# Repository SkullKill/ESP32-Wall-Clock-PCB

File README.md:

# ESP32-Wall-Clock-PCB
ESP32 based 30cm Wall Mounted Clock. WiFi, NTP, SNMP, web interface, MicroUsb, Type-C, HG3613 Retrofit

Can be retrofitted into a HG3613 Case, or use standalone with the wall mounting on the pcb, or in a 3D Printed Case.

3D Printable Case not done yet...

this is still a work in progress.

PCB itself should be final, but the software is still being worked on. 

e.g Code for the light sensitivity sensor to automaticly adjust the display intensity

RTC PCF8563T code. 

OLED coding, etc....

ESP32-Wall-Clock-01.jpg

ESP32-Wall-Clock-Front-RT-V1.0a-WithOLEDboard.jpg

## V 1.0 26/08/2020 - Initial Release

  ------------------------------------------------------------
## PCB Board Used

Ready to use PCB Board (no up yet)

https://www.skstore.com.au/electronics/pcb/ESP32-Wall-Clock

PCB Design Files / gerber files

[ESP32-Wall-Clock-PCB](https://github.com/SkullKill/ESP32-Wall-Clock-PCB)

3D Printed Case design files / STL (no up yet)

[ESP32-Wall-Clock-PCB](https://github.com/SkullKill/ESP32-Wall-Clock-PCB)

FYI Gerber files are in the release section

https://github.com/SkullKill/ESP32-Wall-Clock-PCB/releases

more pictures in the wiki

https://github.com/SkullKill/ESP32-Wall-Clock-PCB/wiki

ESP32-Wall-Clock-HG3613-Retrofit-04.jpg

  ------------------------------------------------------------
## Schematics

ESP32-Wall-Clock-schematics-01-V1.0a.jpg

ESP32-Wall-Clock-schematics-02-V1.0.jpg

ESP32-Wall-Clock-schematics-03-V1.0.jpg

  ------------------------------------------------------------
## MecanicalDrawing

(Not Done Yet)

  ------------------------------------------------------------
## Code Used
(Not Done Yet)
[ESP32-Wall-Clock](https://github.com/SkullKill/ESP32-Wall-Clock)

  ------------------------------------------------------------

PCB features

* ESP32 Microprocessor
* onboard, IO0 / Reset switches
* breakout for UART (Programming/Serial monitor), i2c, SPI, 1-wire
* 5V input via MicroUSB, USB Type-C, 2.1mm barrel, Screw Type Terminal
* OR 5.6V to 26V if using Switchmode Reg, OR 6.4V-30V if using AMS1117-5.0 (input via 2.1mm barrel or Screw Type Terminal)
* PCF8563T RTC Clock with CR2032 Coin Cell Battery
* CP2102 USB to Serial, with Auto Reset (optional)
* RTC clock
* ALS-PT19 Light Intensity Sensor, to adjust Screen Brightness
* AHT20 Temperature / Humidity Sensor
* 1-Wire provision (possibility to add a number of DS18B20 temperature sensors)
* Built in buzzer
* 1-wire rail (possibility to add a number of DS18B20 temperature sensors)
* 2 physical button, + 8 physical button via TM1638, using diode, so that multiple button can be pressed at the same time.
* Ability to add external buttons.
* 1 configurable status light. (IO 13)
* 2 X TM1638 LED Segment Display Driver (in Common Anode Mode) [ one driving 6 digit, one driving 10 digit ]
* 6 X 1.8" / 45mm Segment display for Time Display (Common Anode Mode)
* 0.56" / 14.22mm Segment display for Date/Month / Temperature/Humidity (Common Anode Mode)
* Micro SD Card Slot
* Reverse polarity protection on 12V input
* PTC Fuse
* Level Shifter for ESP32 - TM1638 Comms

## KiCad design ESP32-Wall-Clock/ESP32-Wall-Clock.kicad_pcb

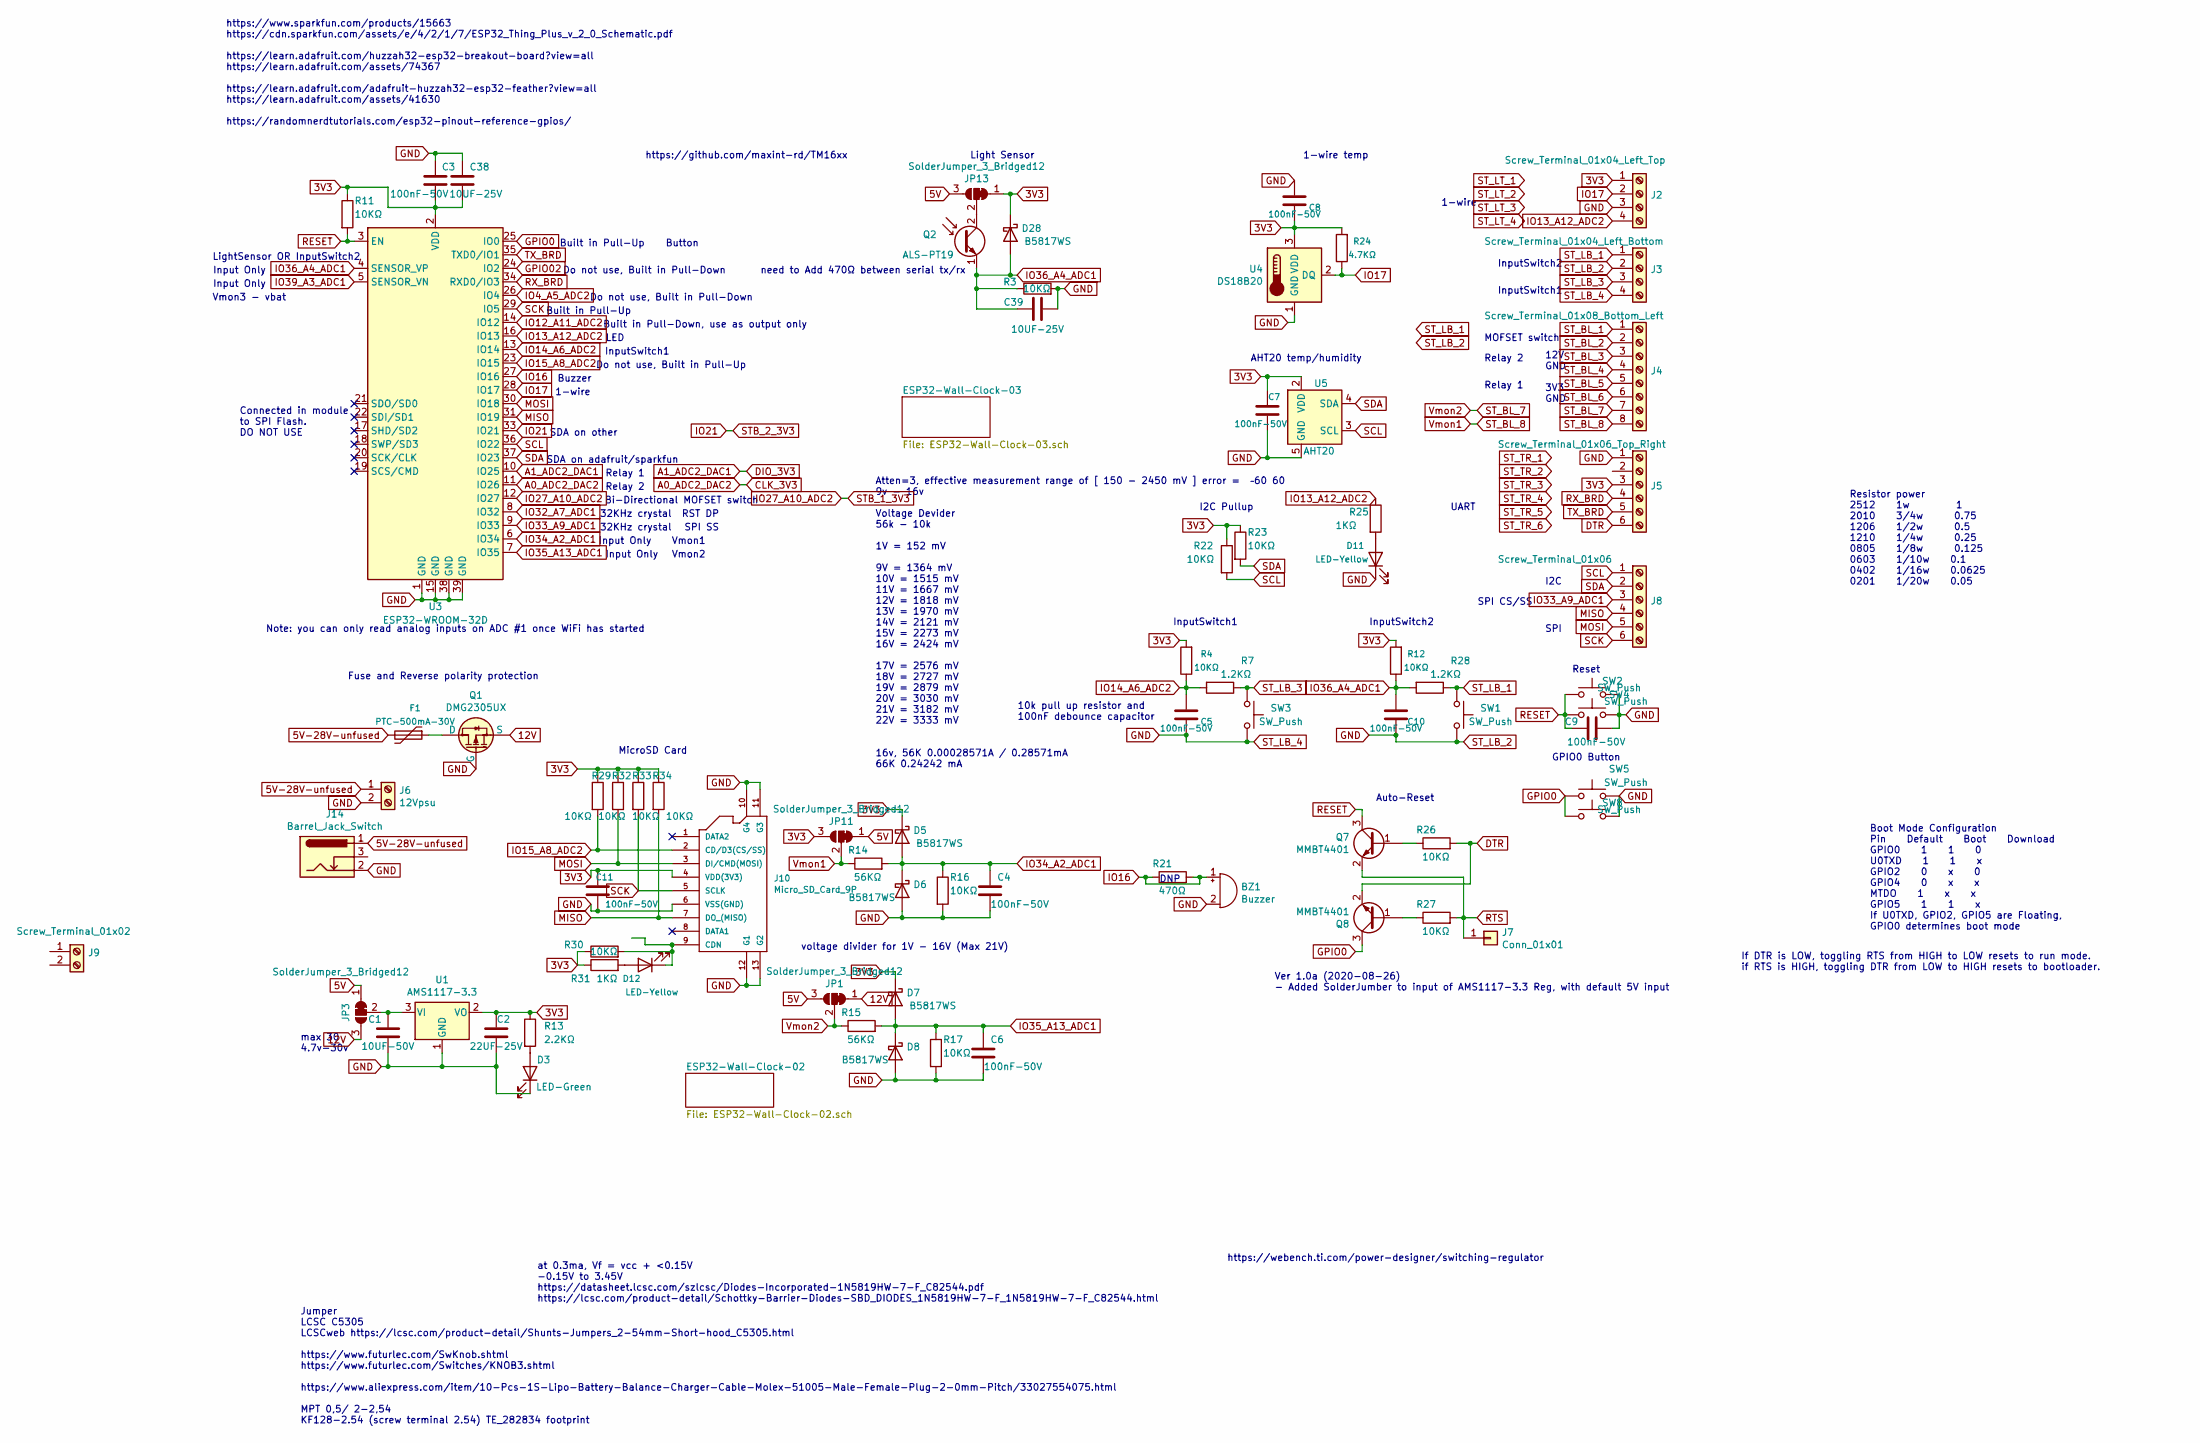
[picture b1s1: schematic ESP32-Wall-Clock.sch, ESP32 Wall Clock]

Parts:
BZ1: Buzzer; Buzzer_12x9.5RM5.0; MPN ZL-YDW1207-4005PA-5.0; LCSC C219727
C1: 10UF-50V; C_1206_3216Metric; MPN CL31A106KBHNNNE; LCSC C13585
C2: 22UF-25V; C_0805_2012Metric; MPN CL21A226MAQNNNE; LCSC C45783
C3, C4, C5, C6, C7, C8, C9, C10, C11: 100nF-50V; C_0603_1608Metric; MPN AC0603KRX7R9BB104; LCSC C149620
C38, C39: 10UF-25V; C_0603_1608Metric; MPN CL10A106MA8NRNC; LCSC C96446
D3: LED-Green; LED_0603_1608Metric; MPN ORH-G36G; LCSC C205443
D5, D6, D7, D8, D28: B5817WS; D_SOD-323; MPN B5817WS-SJ; LCSC C114023
D11, D12: LED-Yellow; LED_0603_1608Metric; MPN FC-DA1608HYK-588J; LCSC C84268
F1: PTC-500mA-30V; Fuse_1812_4532Metric; MPN JK-MSMD050-30; LCSC C369168
J2: Screw_Terminal_01x04_Left_Top; TerminalBlock_TE_282834-4_1x04_P2.54mm_Horizontal; MPN KF128-2.54-4P
J3: Screw_Terminal_01x04_Left_Bottom; TerminalBlock_TE_282834-4_1x04_P2.54mm_Horizontal; MPN KF128-2.54-4P
J4: Screw_Terminal_01x08_Bottom_Left; TerminalBlock_TE_282834-8_1x08_P2.54mm_Horizontal; MPN KF128-2.54-8P
J5: Screw_Terminal_01x06_Top_Right; TerminalBlock_TE_282834-6_1x06_P2.54mm_Horizontal; MPN KF128-2.54-6P
J6: 12Vpsu; TerminalBlock_bornier-2_P5.08mm; MPN WJ126V-5.0-2P; LCSC C8404
J7: Conn_01x01; PinHeader_1x01_P2.54mm_Vertical
J8: Screw_Terminal_01x06; TerminalBlock_TE_282834-6_1x06_P2.54mm_Horizontal; MPN KF128-2.54-6P
J9: Screw_Terminal_01x02; TerminalBlock_TE_282834-2_1x02_P2.54mm_Horizontal; MPN KF128-2.54-2P
J10: Micro_SD_Card_9P; Micro_SD_9+4P-SMD-16.1X14.5X1.85MM; MPN XKTF-015-N; LCSC C381082
J14: Barrel_Jack_Switch; BarrelJack_Wuerth_6941xx301002; MPN DC-005 5.5-2.0MM; LCSC C16214
JP1, JP11, JP13: SolderJumper_3_Bridged12; SolderJumper-3_P1.3mm_Bridged12_RoundedPad1.0x1.5mm
JP3: SolderJumper_3_Bridged12; SolderJumper-3_P1.3mm_Bridged2Bar12_RoundedPad1.0x1.5mm
Q1: DMG2305UX; SOT-23; MPN DMG2305UX-13; LCSC C144153
Q2: ALS-PT19; LED_0603_1608Metric; MPN ALS-PT19-315C/L177/TR8; LCSC C146233
Q7, Q8: MMBT4401; SOT-23; MPN MMBT4401LT1G; LCSC C31776
R3, R4, R11, R12, R16, R17, R22, R23, R26, R27, R29, R30, R32, R33, R34: 10KΩ; R_0603_1608Metric; MPN RC0603FR-0710KL; LCSC C98220
R7, R28: 1.2KΩ; R_0603_1608Metric; MPN RC0603FR-071K2L; LCSC C114605
R13: 2.2KΩ; R_0603_1608Metric; MPN RC0603FR-072K2L; LCSC C114662
R14, R15: 56KΩ; R_0603_1608Metric; MPN RC0603FR-0756KL; LCSC C114630
R21: 470Ω; R_0603_1608Metric; MPN RC0603FR-07470RL; LCSC C114669
R24: 4.7KΩ; R_0603_1608Metric; MPN RC0603FR-074K7L; LCSC C99782
R25, R31: 1KΩ; R_0603_1608Metric; MPN RC0603FR-071KL; LCSC C22548
SW1, SW2, SW3, SW8: SW_Push; SW_Push_1P1T-MP_NO_Horizontal_Alps_SKRTLAE010; MPN SKRTLAE010; LCSC C110293
SW4, SW5: SW_Push; SW_SPST_TL3305A; LCSC C174049
U1: AMS1117-3.3; SOT-223-3_TabPin2; MPN AMS1117-3.3; LCSC C426566
U3: ESP32-WROOM-32D; ESP32-WROOM-32; LCSC C473012
U4: DS18B20; TO-92_Inline; MPN DS18B20+; LCSC C9753
U5: AHT20; MPN AHT20; LCSC C503357

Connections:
3V3: C2.1, C3.1, C7.1, C8.2, C11.1, C38.2, D5.1 (K), D7.1 (K), D28.1 (K), J2.1, J5.3, J10.4 (VDD(3V3)), JP11.3 (B), JP13.1 (A), R4.2, R11.1, R12.2, R13.1, R22.1, R23.1, R24.2, R29.1, R30.1, R31.1, R32.1, R33.1, R34.1, U1.2 (VO), U3.2 (VDD), U4.3 (VDD), U5.2 (VDD); also elsewhere on the board
5V: JP1.3 (B), JP3.1 (A), JP11.1 (A), JP13.3 (B); also elsewhere on the board
5V-28V-unfused: F1.2, J6.1, J14.1
12V: JP1.1 (A), JP3.3 (B), Q1.2 (S); also elsewhere on the board
A0_ADC2_DAC2: U3.11 (IO26); also elsewhere on the board
A1_ADC2_DAC1: U3.10 (IO25); also elsewhere on the board
DTR: J5.6, Q8.2 (E), R26.2; also elsewhere on the board
GND: BZ1.2 (+), C1.2, C2.2, C3.2, C4.2, C5.2, C6.2, C7.2, C8.1, C9.2, C10.2, C11.2, C38.1, C39.2, D3.1 (K), D6.2 (A), D8.2 (A), D11.1 (K), J2.3, J3.2, J3.4, J5.1, J6.2, J10.6 (VSS(GND)), J10.10 (G4), J10.11 (G3), J10.12 (G1), J10.13 (G2), J14.2, Q1.1 (G), R3.2, R16.2, R17.2, SW1.2, SW2.2, SW3.2, SW4.2, SW5.2, SW8.2, U1.1 (GND), U3.1 (GND), U3.15 (GND), U3.38 (GND), U3.39 (GND), U4.1 (GND), U5.5 (GND); also elsewhere on the board
GPIO0: Q8.3 (C), SW5.1, SW8.1, U3.25 (IO0)
GPIO02: U3.24 (IO2)
IO4_A5_ADC2: U3.26 (IO4)
IO12_A11_ADC2: U3.14 (IO12)
IO13_A12_ADC2: J2.4, R25.1, U3.16 (IO13)
IO14_A6_ADC2: C5.1, R4.1, R7.2, U3.13 (IO14)
IO15_A8_ADC2: J10.2 (CD/D3(CS/SS)), R29.2, U3.23 (IO15)
IO16: BZ1.1 (-), R21.1, R21.2, U3.27 (IO16)
IO17: J2.2, R24.1, U3.28 (IO17), U4.2 (DQ)
IO21: U3.33 (IO21); also elsewhere on the board
IO27_A10_ADC2: U3.12 (IO27); also elsewhere on the board
IO32_A7_ADC1: U3.8 (IO32); also elsewhere on the board
IO33_A9_ADC1: J8.3, U3.9 (IO33)
IO34_A2_ADC1: C4.1, D5.2 (A), D6.1 (K), R14.2, R16.1, U3.6 (IO34)
IO35_A13_ADC1: C6.1, D7.2 (A), D8.1 (K), R15.2, R17.1, U3.7 (IO35)
IO36_A4_ADC1: C10.1, C39.1, D28.2 (A), Q2.1 (E), R3.1, R12.1, R28.2, U3.4 (SENSOR_VP)
IO39_A3_ADC1: U3.5 (SENSOR_VN); also elsewhere on the board
MISO: J8.4, J10.7 (DO_(MISO)), R34.2, U3.31 (IO19)
MOSI: J8.5, J10.3 (DI/CMD(MOSI)), R32.2, U3.30 (IO18)
unnamed: C1.1, JP3.2 (C), U1.3 (VI)
unnamed: D3.2 (A), R13.2
unnamed: D11.2 (A), R25.2
unnamed: D12.1 (K), J10.9 (CDN), R30.2
unnamed: D12.2 (A), R31.2
unnamed: F1.1, Q1.3 (D)
unnamed: JP13.2 (C), Q2.2 (C)
unnamed: Q7.1 (B), R26.1
unnamed: Q8.1 (B), R27.1
RESET: C9.1, Q7.3 (C), R11.2, SW2.1, SW4.1, U3.3 (EN); also elsewhere on the board
RTS: J7.1, Q7.2 (E), R27.2; also elsewhere on the board
RX_BRD: J5.4, U3.34 (RXD0/IO3); also elsewhere on the board
SCK: J8.6, J10.5 (SCLK), R33.2, U3.29 (IO5)
SCL: J8.1, R22.2, U3.36 (IO22), U5.3 (SCL); also elsewhere on the board
SDA: J8.2, R23.2, U3.37 (IO23), U5.4 (SDA); also elsewhere on the board
ST_BL_7: J4.7, JP1.2 (C), R15.1
ST_BL_8: J4.8, JP11.2 (C), R14.1
ST_LB_1: J3.1, R28.1, SW1.1
ST_LB_3: J3.3, R7.1, SW3.1
TX_BRD: J5.5, U3.35 (TXD0/IO1); also elsewhere on the board

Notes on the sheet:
https://webench.ti.com/power-designer/switching-regulator
Ver 1.0a (2020-08-26) - Added SolderJumber to input of AMS1117-3.3 Reg, with default 5V input
10k pull up resistor and 100nF debounce capacitor
Jumper LCSC C5305 LCSCweb https://lcsc.com/product-detail/Shunts-Jumpers_2-54mm-Short-hood_C5305.html https://www.futurlec.com/SwKnob.shtml https://www.futurlec.com/Switches/KNOB3.shtml https://www.aliexpress.com/item/10-Pcs-1S-Lipo-Battery-Balance-Charger-Cable-Molex-51005-Male-Female-Plug-2-0mm-P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
Fuse and Reverse polarity protection
Resistor power 2512 1w 1 2010 3/4w 0.75 1206 1/2w 0.5 1210 1/4w 0.25 0805 1/8w 0.125 0603 1/10w 0.1 0402 1/16w 0.0625 0201 1/20w 0.05
12V GND 3V3 GND
MOFSET switch
InputSwitch1
max 30 4.7v-30v
UART
Relay 1
Atten=3, effective measurement range of [ 150 - 2450 mV ] error = –60 60 9v - 16v Voltage Devider 56k - 10k 1V = 152 mV 9V = 1364 mV 10V = 1515 mV 11V = 1667 mV 12V = 1818 mV 13V = 1970 mV 14V = 2121 mV 15V = 2273 mV 16V = 2424 mV 17V = 2576 mV 18V = 2727 mV 19V = 2879 mV 20V = 3030 mV 21V = 3182 m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
at 0.3ma, Vf = vcc + <0.15V -0.15V to 3.45V https://datasheet.lcsc.com/szlcsc/Diodes-Incorporated-1N5819HW-7-F_C82544.pdf https://lcsc.com/product-detail/Schottky-Barrier-Diodes-SBD_DIODES_1N5819HW-7-F_1N5819HW-7-F_C82544.html
https://www.sparkfun.com/products/15663 https://cdn.sparkfun.com/assets/e/4/2/1/7/ESP32_Thing_Plus_v_2_0_Schematic.pdf https://learn.adafruit.com/huzzah32-esp32-breakout-board?view=all https://learn.adafruit.com/assets/74367 https://learn.adafruit.com/adafruit-huzzah32-esp32-feather?view=all https: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
Reset
GPIO0 Button
If DTR is LOW, toggling RTS from HIGH to LOW resets to run mode. if RTS is HIGH, toggling DTR from LOW to HIGH resets to bootloader.
Auto-Reset
Boot Mode Configuration Pin Default Boot Download GPIO0 1 1 0 U0TXD 1 1 x GPIO2 0 x 0 GPIO4 0 x x MTDO 1 x x GPIO5 1 1 x If U0TXD, GPIO2, GPIO5 are Floating, GPIO0 determines boot mode
Vmon1
LED
Button
Note: you can only read analog inputs on ADC #1 once WiFi has started
Input Only
Built in Pull-Down, use as output only
32KHz crystal
1-wire
Buzzer
DNP
Do not use, Built in Pull-Down
Do not use, Built in Pull-Up
Built in Pull-Up
voltage divider for 1V - 16V (Max 21V)
AHT20 temp/humidity
Vmon2
Bi-Directional MOFSET switch
1-wire temp
SDA on adafruit/sparkfun
I2C Pullup

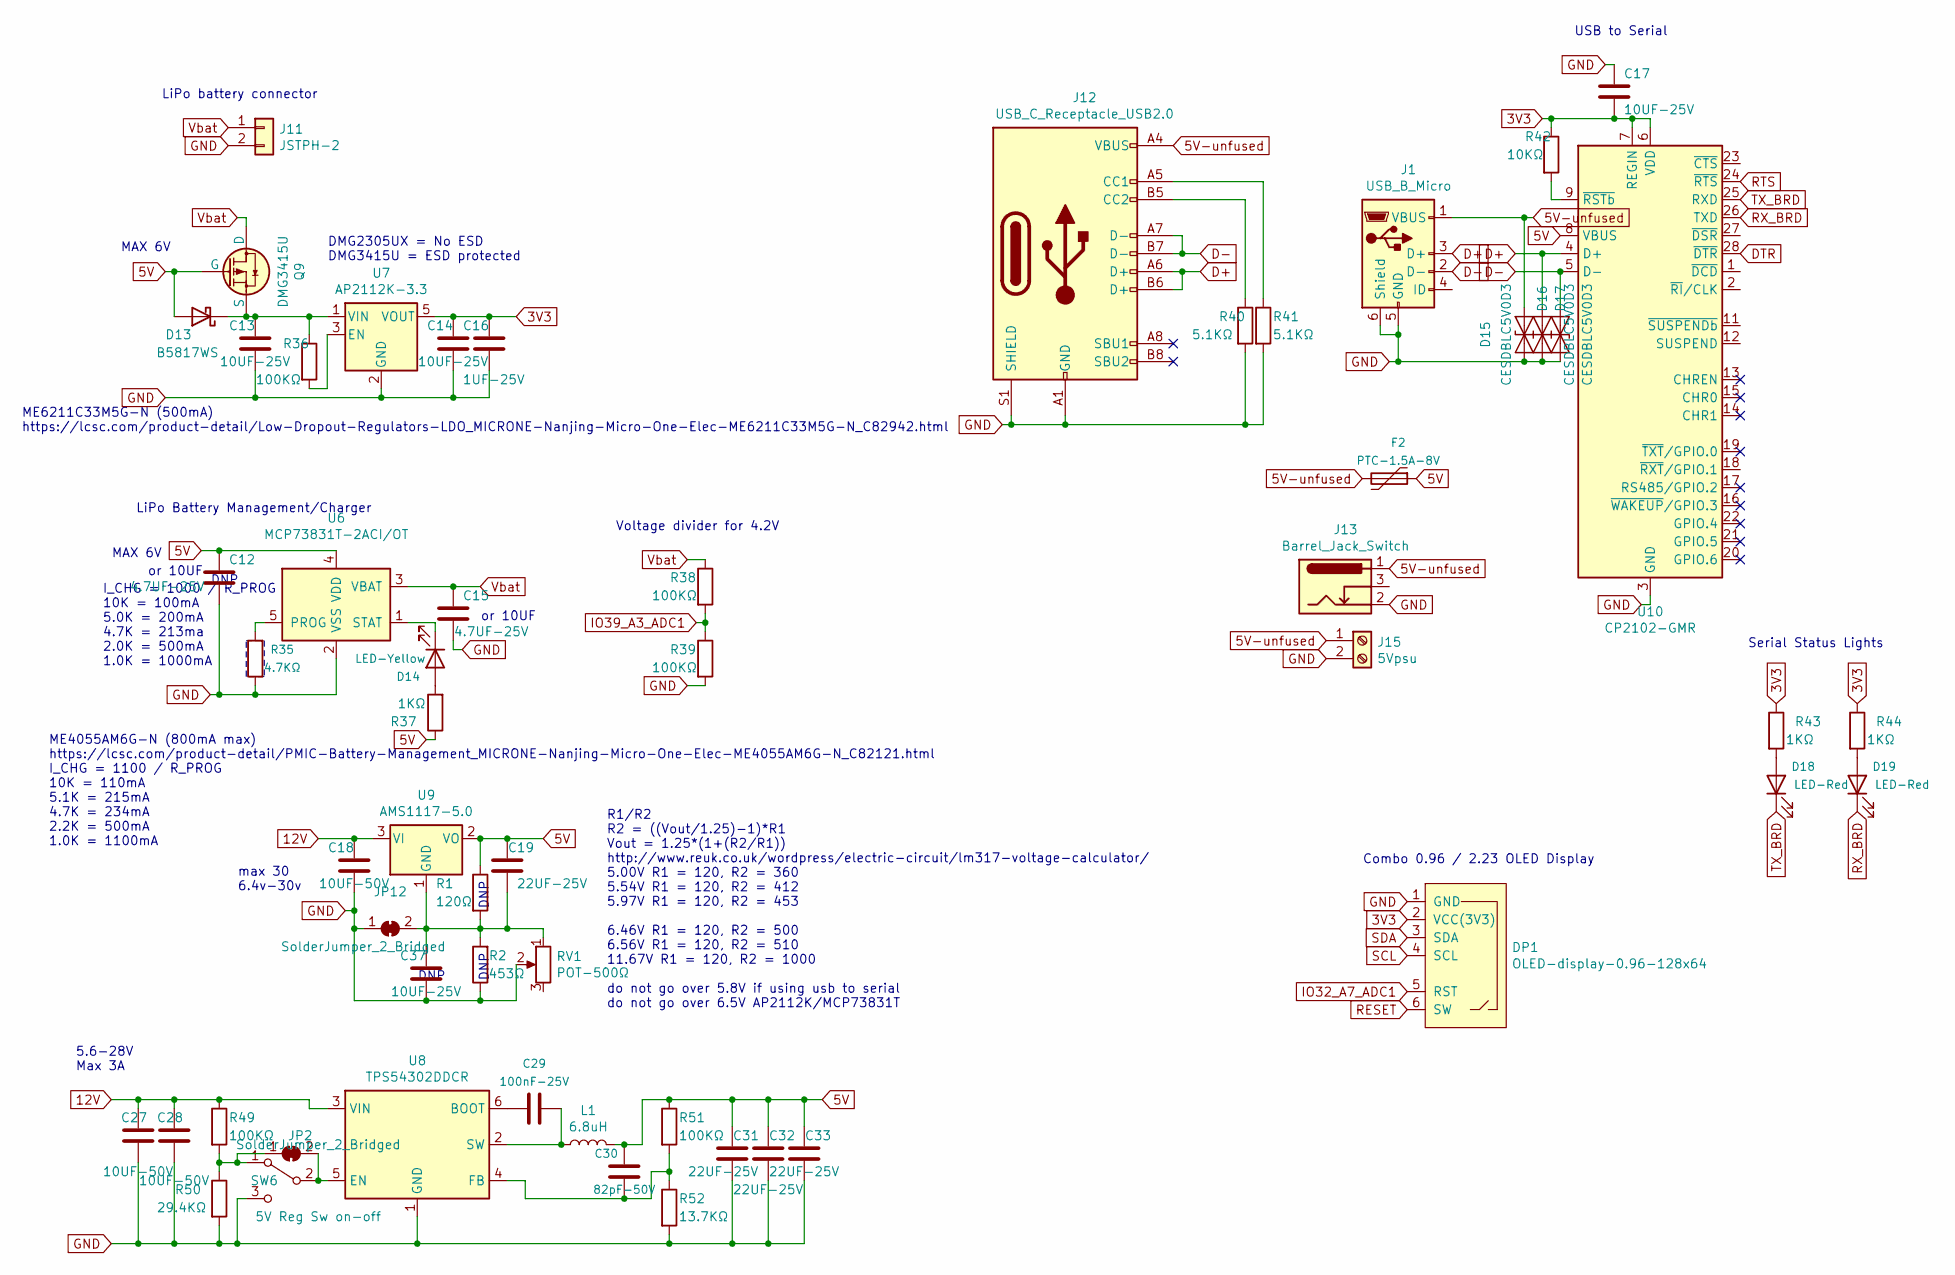
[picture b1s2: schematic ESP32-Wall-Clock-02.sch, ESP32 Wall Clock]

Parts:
C12, C15: 4.7UF-25V; C_0603_1608Metric; MPN CL10A475KA8NQNC; LCSC C69335
C13, C14, C17, C37: 10UF-25V; C_0603_1608Metric; MPN CL10A106MA8NRNC; LCSC C96446
C16: 1UF-25V; C_0603_1608Metric; MPN CL10B105KA8NNNC; LCSC C29936
C18, C27, C28: 10UF-50V; C_1206_3216Metric; MPN CL31A106KBHNNNE; LCSC C13585
C19, C31, C32, C33: 22UF-25V; C_0805_2012Metric; MPN CL21A226MAQNNNE; LCSC C45783
C29: 100nF-25V; C_0402_1005Metric; MPN CL05A104KA5NNNC; LCSC C100072
C30: 82pF-50V; C_0402_1005Metric; MPN CL05C820JB5NNNC; LCSC C13532
D13: B5817WS; D_SOD-323; MPN B5817WS-SJ; LCSC C114023
D14: LED-Yellow; LED_0603_1608Metric; MPN FC-DA1608HYK-588J; LCSC C84268
D15, D16, D17: CESDBLC5V0D3; D_SOD-323; MPN CESDBLC5V0D3; LCSC C47346
D18, D19: LED-Red; LED_0603_1608Metric; MPN FC-DA1608HRK-620D; LCSC C84263
DP1: OLED-display-0.96-128x64; OLED-display-0.96-128x64-2.23-128x32-combo
F2: PTC-1.5A-8V; Fuse_1812_4532Metric; MPN 1812L150ZR; LCSC C207071
J1: USB_B_Micro; USB_Micro-B_Korean_U-F-M5DD-Y-L; MPN U-F-M5DD-Y-L; LCSC C91146
J11: JSTPH-2; JST_PH_S2B-PH-K_1x02_P2.00mm_Horizontal; MPN S2B-PH-K-S; LCSC C49992
J12: USB_C_Receptacle_USB2.0; USB_C_Receptacle_HRO_TYPE-C-31-M-12; MPN TYPE-C-31-M-12; LCSC C165948
J13: Barrel_Jack_Switch; BarrelJack_Wuerth_6941xx301002; MPN DC-005 5.5-2.0MM; LCSC C16214
J15: 5Vpsu; TerminalBlock_bornier-2_P5.08mm; MPN WJ126V-5.0-2P; LCSC C8404
JP2: SolderJumper_2_Bridged; SolderJumper-2_P1.3mm_Bridged_RoundedPad1.0x1.5mm
JP12: SolderJumper_2_Bridged; SolderJumper-2_P1.3mm_Bridged2Bar_RoundedPad1.0x1.5mm
L1: 6.8uH; L_7.3x7.3_H4.5; MPN FXL0630-6R8-M; LCSC C167221
Q9: DMG3415U; SOT-23; MPN DMG3415U-7; LCSC C96616
R1: 120Ω; R_0603_1608Metric; MPN RC0603FR-07120RL; LCSC C114640
R2: 453Ω; R_0603_1608Metric; MPN RC0603FR-07453RL; LCSC C482871
R35: 4.7KΩ; R_0603_1608Metric; MPN RC0603FR-074K7L; LCSC C99782
R36, R38, R39, R49, R51: 100KΩ; R_0603_1608Metric; MPN RC0603FR-07100KL; LCSC C14675
R37, R43, R44: 1KΩ; R_0603_1608Metric; MPN RC0603FR-071KL; LCSC C22548
R40, R41: 5.1KΩ; R_0603_1608Metric; MPN RC0603FR-075K1L; LCSC C105580
R42: 10KΩ; R_0603_1608Metric; MPN RC0603FR-0710KL; LCSC C98220
R50: 29.4KΩ; R_0603_1608Metric; MPN RC0603FR-0729K4L; LCSC C137752
R52: 13.7KΩ; R_0603_1608Metric; MPN RC0603FR-0713K7L; LCSC C482771
RV1: POT-500Ω; Potentiometer_Bourns_TC33X_Vertical; MPN VG039NCHXTB501; LCSC C128556
SW6: 5V Reg Sw on-off; SW_SPDT_PCM12; MPN K3-1296S-E2; LCSC C136659
U6: MCP73831T-2ACI/OT; SOT-23-5; MPN MCP73831T-2ACI/OT; LCSC C424093
U7: AP2112K-3.3; SOT-23-5; MPN AP2112K-3.3TRG1; LCSC C51118
U8: TPS54302DDCR; SOT-23-6; MPN TPS54302DDCR; LCSC C311983
U9: AMS1117-5.0; SOT-223-3_TabPin2; MPN AMS1117-5.0; LCSC C473812
U10: CP2102-GMR; QFN-28-1EP_5x5mm_P0.5mm_EP3.35x3.35mm; MPN CP2102-GMR; LCSC C6568

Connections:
3V3: C14.1, C16.1, C17.2, DP1.2 (VCC(3V3)), R42.1, R43.1, R44.1, U7.5 (VOUT), U10.6 (VDD), U10.7 (REGIN); also elsewhere on the board
5V: C12.1, C19.1, C30.1, C31.1, C32.1, C33.1, D13.2 (A), F2.1, L1.2, Q9.1 (G), R1.1, R37.1, R51.1, U6.4 (VDD), U9.2 (VO), U10.8 (VBUS); also elsewhere on the board
5V-unfused: D15.2 (A2), F2.2, J1.1 (VBUS), J12.A4 (VBUS), J12.A9 (VBUS), J12.B4 (VBUS), J12.B9 (VBUS), J13.1, J15.1
12V: C18.1, C27.1, C28.1, R49.1, U8.3 (VIN), U9.3 (VI); also elsewhere on the board
D+: D16.2 (A2), J1.3 (D+), J12.A6 (D+), J12.B6 (D+), U10.4 (D+)
D-: D17.2 (A2), J1.2 (D-), J12.A7 (D-), J12.B7 (D-), U10.5 (D-)
DTR: U10.28 (~DTR); also elsewhere on the board
GND: C12.2, C13.2, C14.2, C15.2, C16.2, C17.1, C18.2, C27.2, C28.2, C31.2, C32.2, C33.2, C37.2, D15.1 (A1), D16.1 (A1), D17.1 (A1), DP1.1 (GND), J1.5 (GND), J1.6 (Shield), J11.2, J12.A1 (GND), J12.A12 (GND), J12.B1 (GND), J12.B12 (GND), J12.S1 (SHIELD), J13.2, J15.2, JP12.1 (A), R2.1, R35.1, R39.2, R40.2, R41.2, R50.2, R52.2, RV1.2, SW6.3 (C), U6.2 (VSS), U7.2 (GND), U8.1 (GND), U10.3 (GND), U10.29 (GND); also elsewhere on the board
IO32_A7_ADC1: DP1.5 (RST); also elsewhere on the board
IO39_A3_ADC1: R38.2, R39.1; also elsewhere on the board
unnamed: C13.1, D13.1 (K), Q9.2 (S), R36.1, U7.1 (VIN)
unnamed: C19.2, C37.1, JP12.2 (B), R1.2, R2.2, RV1.1, U9.1 (GND)
unnamed: C29.1, U8.6 (BOOT)
unnamed: C29.2, L1.1, U8.2 (SW)
unnamed: C30.2, R51.2, R52.1, U8.4 (FB)
unnamed: D14.1 (K), U6.1 (STAT)
unnamed: D14.2 (A), R37.2
unnamed: D18.2 (A), R43.2
unnamed: D19.2 (A), R44.2
unnamed: J12.A5 (CC1), R41.1
unnamed: J12.B5 (CC2), R40.1
unnamed: JP2.1 (A), R49.2, R50.1, SW6.1 (A)
unnamed: JP2.2 (B), SW6.2 (B), U8.5 (EN)
unnamed: R35.2, U6.5 (PROG)
unnamed: R36.2, U7.3 (EN)
unnamed: R42.2, U10.9 (~RSTb)
RESET: DP1.6 (SW); also elsewhere on the board
RTS: U10.24 (~RTS); also elsewhere on the board
RX_BRD: D19.1 (K), U10.26 (TXD); also elsewhere on the board
SCL: DP1.4 (SCL); also elsewhere on the board
SDA: DP1.3 (SDA); also elsewhere on the board
TX_BRD: D18.1 (K), U10.25 (RXD); also elsewhere on the board
Vbat: C15.1, J11.1, Q9.3 (D), R38.1, U6.3 (VBAT)

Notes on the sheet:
MAX 6V
I_CHG = 1000 / R_PROG 10K = 100mA 5.0K = 200mA 4.7K = 213ma 2.0K = 500mA 1.0K = 1000mA
DNP
or 10UF
ME4055AM6G-N (800mA max) https://lcsc.com/product-detail/PMIC-Battery-Management_MICRONE-Nanjing-Micro-One-Elec-ME4055AM6G-N_C82121.html I_CHG = 1100 / R_PROG 10K = 110mA 5.1K = 215mA 4.7K = 234mA 2.2K = 500mA 1.0K = 1100mA
DMG2305UX = No ESD DMG3415U = ESD protected
5.6-28V Max 3A
max 30 6.4v-30v
ME6211C33M5G-N (500mA) https://lcsc.com/product-detail/Low-Dropout-Regulators-LDO_MICRONE-Nanjing-Micro-One-Elec-ME6211C33M5G-N_C82942.html
R1/R2 R2 = ((Vout/1.25)-1)*R1 Vout = 1.25*(1+(R2/R1)) http://www.reuk.co.uk/wordpress/electric-circuit/lm317-voltage-calculator/ 5.00V R1 = 120, R2 = 360 5.54V R1 = 120, R2 = 412 5.97V R1 = 120, R2 = 453 6.46V R1 = 120, R2 = 500 6.56V R1 = 120, R2 = 510 11.67V R1 = 120, R2 = 1000 do not go over 5.8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
Voltage divider for 4.2V
Combo 0.96 / 2.23 OLED Display
LiPo battery connector
LiPo Battery Management/Charger
USB to Serial
Serial Status Lights

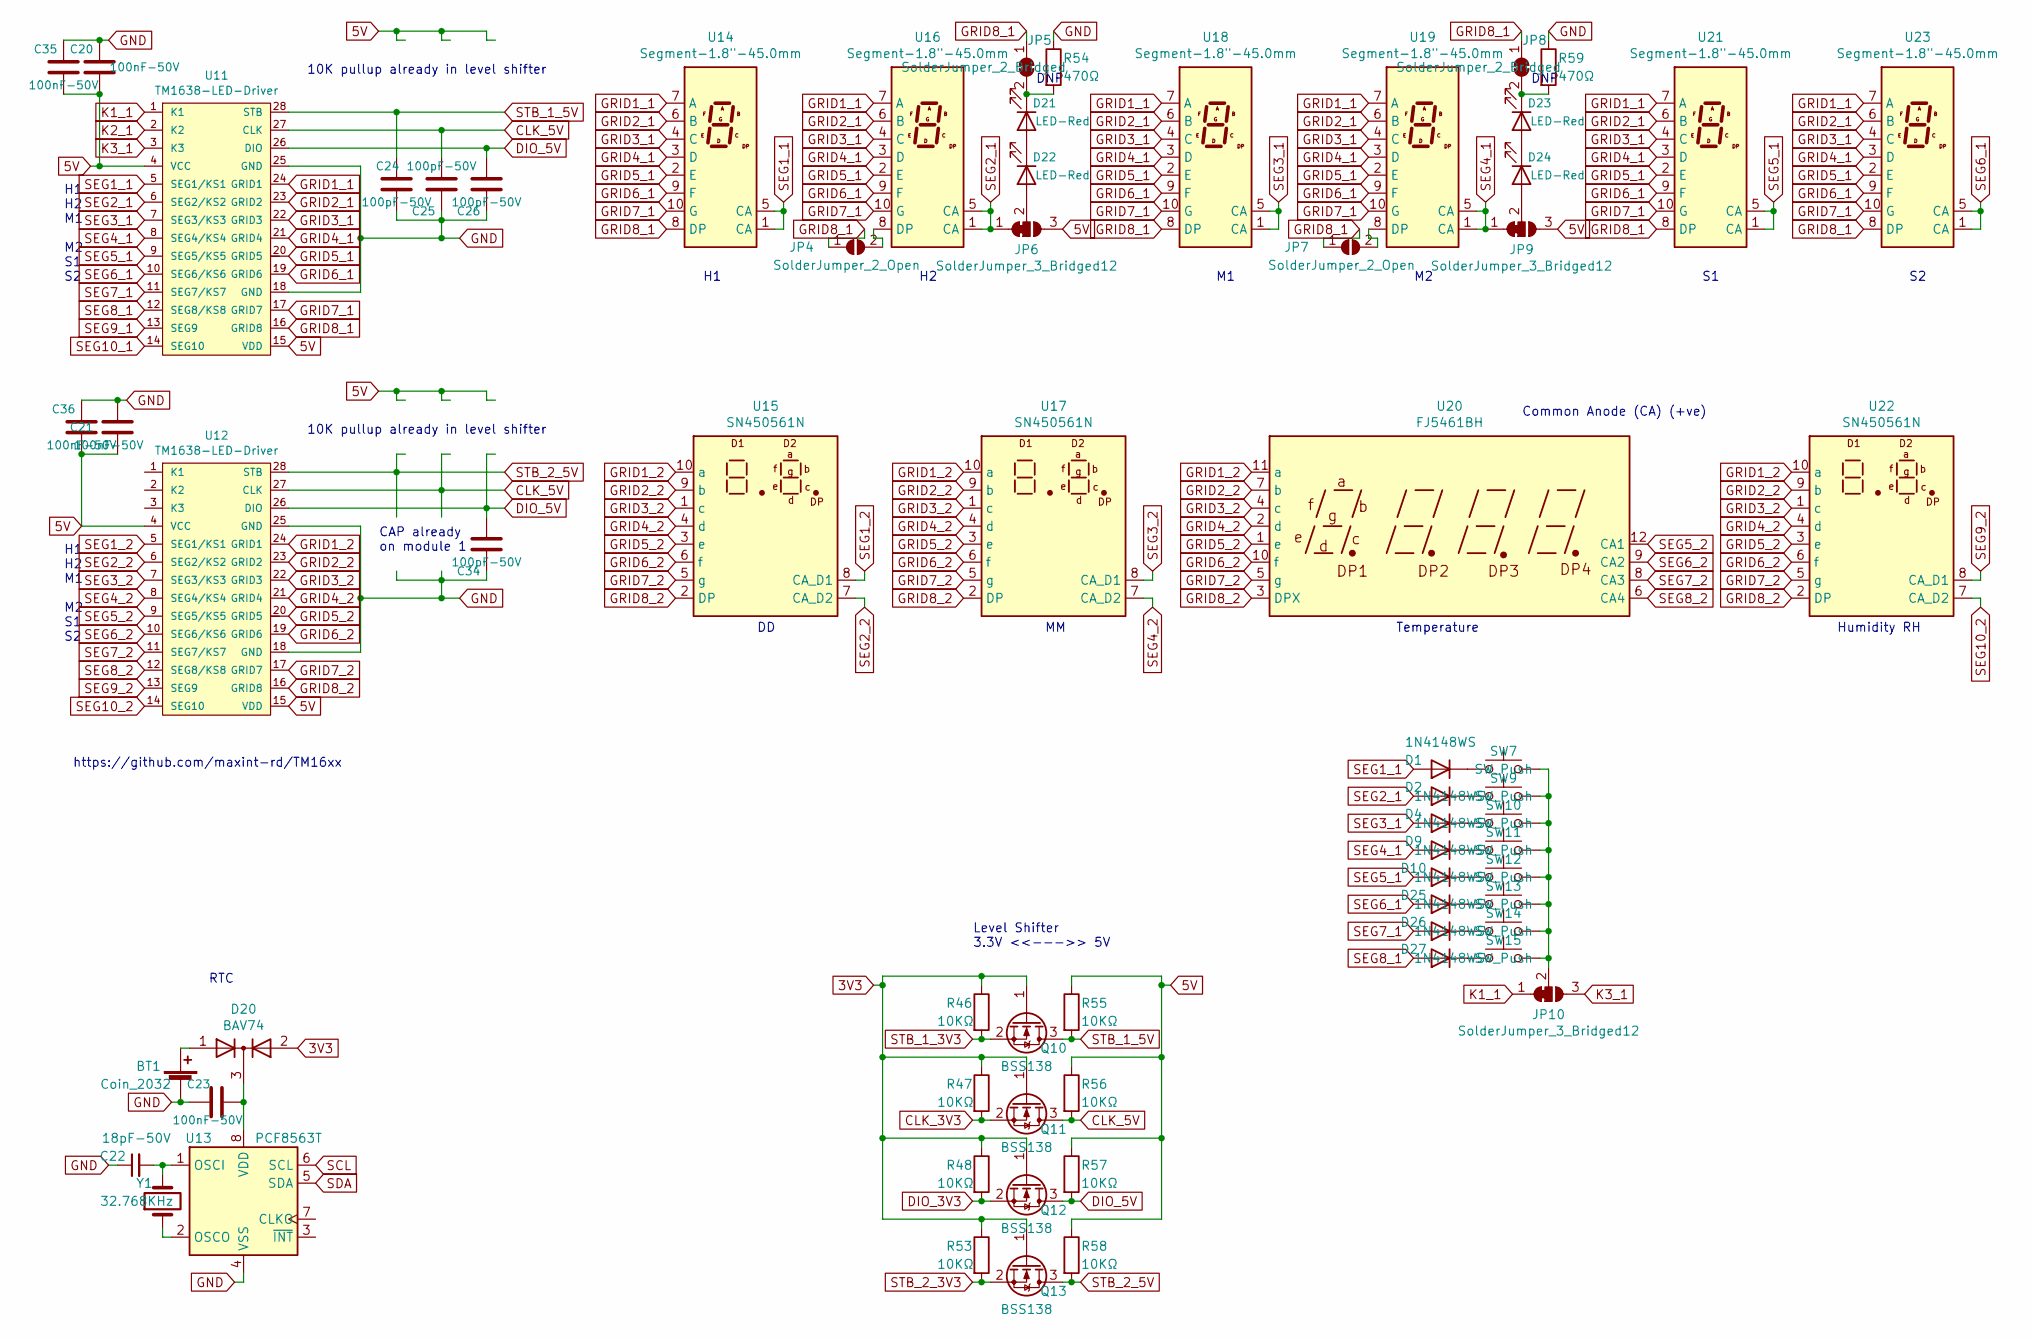
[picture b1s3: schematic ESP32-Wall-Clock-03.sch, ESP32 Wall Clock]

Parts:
BT1: Coin_2032; BatteryHolder_Keystone_1060_1x2032; MPN CR2032-BS-6-1; LCSC C70377
C20, C21, C23, C35, C36: 100nF-50V; C_0603_1608Metric; MPN AC0603KRX7R9BB104; LCSC C149620
C22: 18pF-50V; C_0402_1005Metric; MPN GCM1555C1H180JA16D; LCSC C126499
C24, C25, C26, C34: 100pF-50V; C_0402_1005Metric; MPN CL05C101JB5NNNC; LCSC C26409
D1, D2, D4, D9, D10, D25, D26, D27: 1N4148WS; D_SOD-323; MPN 1N4148WS; LCSC C2128
D20: BAV74; SOT-23; MPN BAV74; LCSC C68981
D21, D22, D23, D24: LED-Red; LED_0603_1608Metric; MPN FC-DA1608HRK-620D; LCSC C84263
JP4, JP7: SolderJumper_2_Open; SolderJumper-2_P1.3mm_Open_RoundedPad1.0x1.5mm
JP5, JP8: SolderJumper_2_Bridged; SolderJumper-2_P1.3mm_Bridged_RoundedPad1.0x1.5mm
JP6, JP9, JP10: SolderJumper_3_Bridged12; SolderJumper-3_P1.3mm_Bridged12_RoundedPad1.0x1.5mm
Q10, Q11, Q12, Q13: BSS138; SOT-23; MPN BSS138-7-F; LCSC C40912
R46, R47, R48, R53, R55, R56, R57, R58: 10KΩ; R_0603_1608Metric; MPN RC0603FR-0710KL; LCSC C98220
R54, R59: 470Ω; R_0603_1608Metric; MPN RC0603FR-07470RL; LCSC C114669
SW7, SW9, SW10, SW11, SW12, SW13, SW14, SW15: SW_Push; SW_Push_1P1T-MP_NO_Horizontal_Alps_SKRTLAE010; MPN SKRTLAE010; LCSC C110293
U11, U12: TM1638-LED-Driver; SOIC-28W_7.5x17.9mm_P1.27mm; MPN TM1638; LCSC C19187
U13: PCF8563T; SOIC-8_3.9x4.9mm_P1.27mm; MPN PCF8563T/5,518; LCSC C7440
U14, U16, U18, U19, U21, U23: Segment-1.8\"-45.0mm; SM471801N; MPN SM471801N; LCSC C193718
U15, U17, U22: SN450561N; MPN SN450561N; LCSC C193143
U20: FJ5461BH; CA56-12SRWA; MPN C38183; LCSC C38183
Y1: 32.768KHz; Crystal_SMD_3215-2Pin_3.2x1.5mm; MPN X321532768KGB2SI; LCSC C94279

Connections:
3V3: D20.2 (A), Q10.1 (G), Q11.1 (G), Q12.1 (G), Q13.1 (G), R46.1, R47.1, R48.1, R53.1; also elsewhere on the board
5V: C20.2, C21.2, C35.2, C36.2, JP6.3 (B), JP9.3 (B), R55.1, R56.1, R57.1, R58.1, U11.4 (VCC), U11.15 (VDD), U12.4 (VCC), U12.15 (VDD); also elsewhere on the board
A0_ADC2_DAC2: Q11.2 (S), R47.2; also elsewhere on the board
A1_ADC2_DAC1: Q12.2 (S), R48.2; also elsewhere on the board
CLK_5V: C25.1, Q11.3 (D), R56.2, U11.27 (CLK), U12.27 (CLK)
DIO_5V: C26.1, C34.1, Q12.3 (D), R57.2, U11.26 (DIO), U12.26 (DIO)
GND: BT1.2 (-), C20.1, C21.1, C22.1, C23.2, C24.2, C25.2, C26.2, C34.2, C35.1, C36.1, R54.1, R59.1, U11.18 (GND), U11.25 (GND), U12.18 (GND), U12.25 (GND), U13.4 (VSS); also elsewhere on the board
GRID1_1: U11.24 (GRID1), U14.7 (A), U16.7 (A), U18.7 (A), U19.7 (A), U21.7 (A), U23.7 (A)
GRID1_2: U12.24 (GRID1), U15.10 (a), U17.10 (a), U20.11 (a), U22.10 (a)
GRID2_1: U11.23 (GRID2), U14.6 (B), U16.6 (B), U18.6 (B), U19.6 (B), U21.6 (B), U23.6 (B)
GRID2_2: U12.23 (GRID2), U15.9 (b), U17.9 (b), U20.7 (b), U22.9 (b)
GRID3_1: U11.22 (GRID3), U14.4 (C), U16.4 (C), U18.4 (C), U19.4 (C), U21.4 (C), U23.4 (C)
GRID3_2: U12.22 (GRID3), U15.1 (c), U17.1 (c), U20.4 (c), U22.1 (c)
GRID4_1: U11.21 (GRID4), U14.3 (D), U16.3 (D), U18.3 (D), U19.3 (D), U21.3 (D), U23.3 (D)
GRID4_2: U12.21 (GRID4), U15.4 (d), U17.4 (d), U20.2 (d), U22.4 (d)
GRID5_1: U11.20 (GRID5), U14.2 (E), U16.2 (E), U18.2 (E), U19.2 (E), U21.2 (E), U23.2 (E)
GRID5_2: U12.20 (GRID5), U15.3 (e), U17.3 (e), U20.1 (e), U22.3 (e)
GRID6_1: U11.19 (GRID6), U14.9 (F), U16.9 (F), U18.9 (F), U19.9 (F), U21.9 (F), U23.9 (F)
GRID6_2: U12.19 (GRID6), U15.6 (f), U17.6 (f), U20.10 (f), U22.6 (f)
GRID7_1: U11.17 (GRID7), U14.10 (G), U16.10 (G), U18.10 (G), U19.10 (G), U21.10 (G), U23.10 (G)
GRID7_2: U12.17 (GRID7), U15.5 (g), U17.5 (g), U20.5 (g), U22.5 (g)
GRID8_2: U12.16 (GRID8), U15.2 (DP), U17.2 (DP), U20.3 (DPX), U22.2 (DP)
IO21: Q13.2 (S), R53.2; also elsewhere on the board
IO27_A10_ADC2: Q10.2 (S), R46.2; also elsewhere on the board
K1_1: JP10.1 (A), U11.1 (K1)
K2_1: U11.2 (K2)
K3_1: JP10.3 (B), U11.3 (K3)
unnamed: BT1.1 (+), D20.1 (A)
unnamed: C22.2, U13.1 (OSCI), Y1.2
unnamed: C23.1, D20.3 (K), U13.8 (VDD)
unnamed: D1.1 (K), SW7.1
unnamed: D2.1 (K), SW9.1
unnamed: D4.1 (K), SW10.1
unnamed: D9.1 (K), SW11.1
unnamed: D10.1 (K), SW12.1
unnamed: D21.1 (K), JP5.2 (B), R54.2
unnamed: D21.2 (A), D22.1 (K)
unnamed: D22.2 (A), JP6.2 (C)
unnamed: D23.1 (K), JP8.2 (B), R59.2
unnamed: D23.2 (A), D24.1 (K)
unnamed: D24.2 (A), JP9.2 (C)
unnamed: D25.1 (K), SW13.1
unnamed: D26.1 (K), SW14.1
unnamed: D27.1 (K), SW15.1
unnamed: JP10.2 (C), SW7.2, SW9.2, SW10.2, SW11.2, SW12.2, SW13.2, SW14.2, SW15.2
unnamed: U13.2 (OSCO), Y1.1
SCL: U13.6 (SCL); also elsewhere on the board
SDA: U13.5 (SDA); also elsewhere on the board
SEG1_2: U12.5 (SEG1/KS1), U15.8 (CA_D1)
SEG2_2: U12.6 (SEG2/KS2), U15.7 (CA_D2)
SEG3_2: U12.7 (SEG3/KS3), U17.8 (CA_D1)
SEG4_2: U12.8 (SEG4/KS4), U17.7 (CA_D2)
SEG5_2: U12.9 (SEG5/KS5), U20.12 (CA1)
SEG6_2: U12.10 (SEG6/KS6), U20.9 (CA2)
SEG7_1: D26.2 (A), U11.11 (SEG7/KS7)
SEG7_2: U12.11 (SEG7/KS7), U20.8 (CA3)
SEG8_1: D27.2 (A), U11.12 (SEG8/KS8)
SEG8_2: U12.12 (SEG8/KS8), U20.6 (CA4)
SEG9_1: U11.13 (SEG9)
SEG9_2: U12.13 (SEG9), U22.8 (CA_D1)
SEG10_1: U11.14 (SEG10)
SEG10_2: U12.14 (SEG10), U22.7 (CA_D2)
STB_1_5V: C24.1, Q10.3 (D), R55.2, U11.28 (STB)
STB_2_5V: Q13.3 (D), R58.2, U12.28 (STB)

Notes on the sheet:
H1 H2 M1 M2 S1 S2
Level Shifter 3.3V <<--->> 5V
10K pullup already in level shifter
DNP
CAP already on module 1
Humidity RH
Temperature
Common Anode (CA) (+ve)
https://github.com/maxint-rd/TM16xx
RTC

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
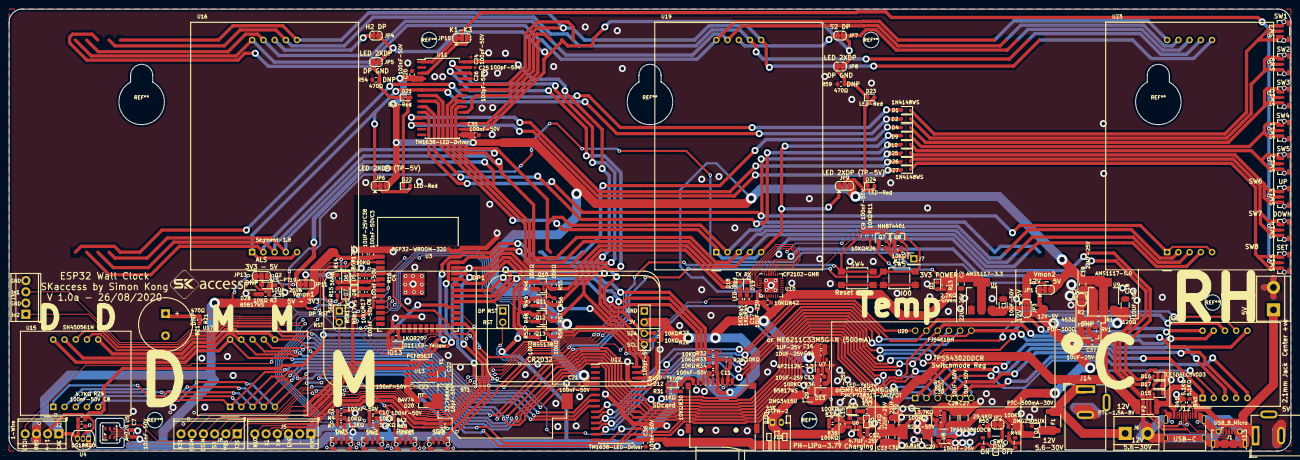
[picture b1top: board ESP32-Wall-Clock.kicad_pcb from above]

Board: 2 copper layers, 290.0 x 100.0 mm, 194 parts (0 on the bottom side), 123 nets.
